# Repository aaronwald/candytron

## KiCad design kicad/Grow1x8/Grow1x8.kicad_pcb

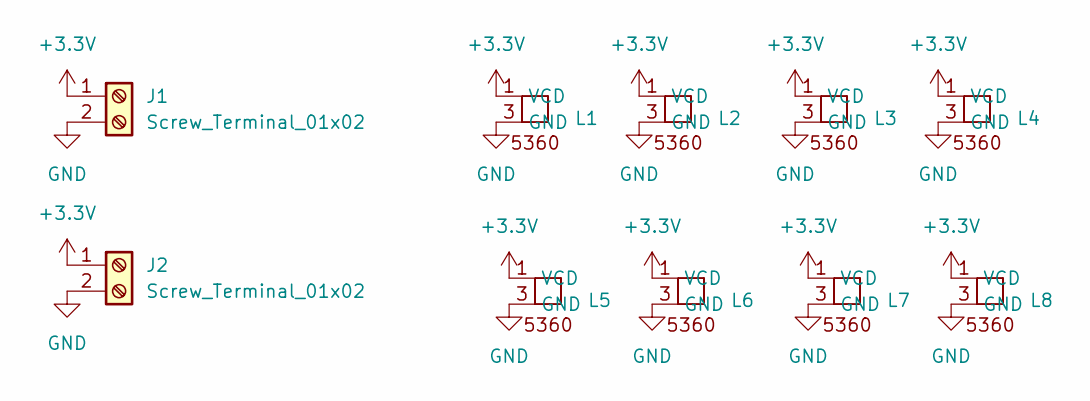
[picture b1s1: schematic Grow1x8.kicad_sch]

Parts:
J1, J2: Screw_Terminal_01x02; TerminalBlock_MetzConnect_Type011_RT05502HBWC_1x02_P5.00mm_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
L1, L2, L3, L4, L5, L6, L7, L8: LED 5630

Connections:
+3.3V: J1.1, J2.1, L1.1 (VCD), L2.1 (VCD), L3.1 (VCD), L4.1 (VCD), L5.1 (VCD), L6.1 (VCD), L7.1 (VCD), L8.1 (VCD)
GND: J1.2, J2.2, L1.3 (GND), L2.3 (GND), L3.3 (GND), L4.3 (GND), L5.3 (GND), L6.3 (GND), L7.3 (GND), L8.3 (GND)

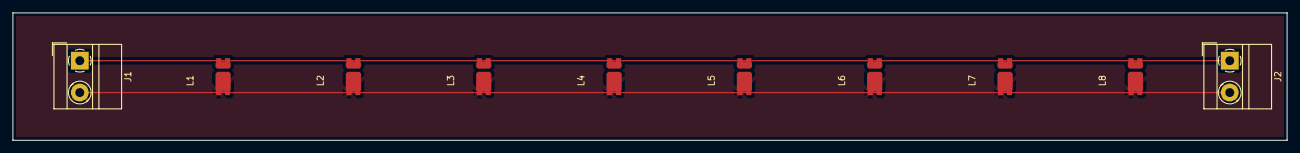
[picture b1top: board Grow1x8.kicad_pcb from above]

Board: 2 copper layers, 200.0 x 20.0 mm, 10 parts (0 on the bottom side), 2 nets.

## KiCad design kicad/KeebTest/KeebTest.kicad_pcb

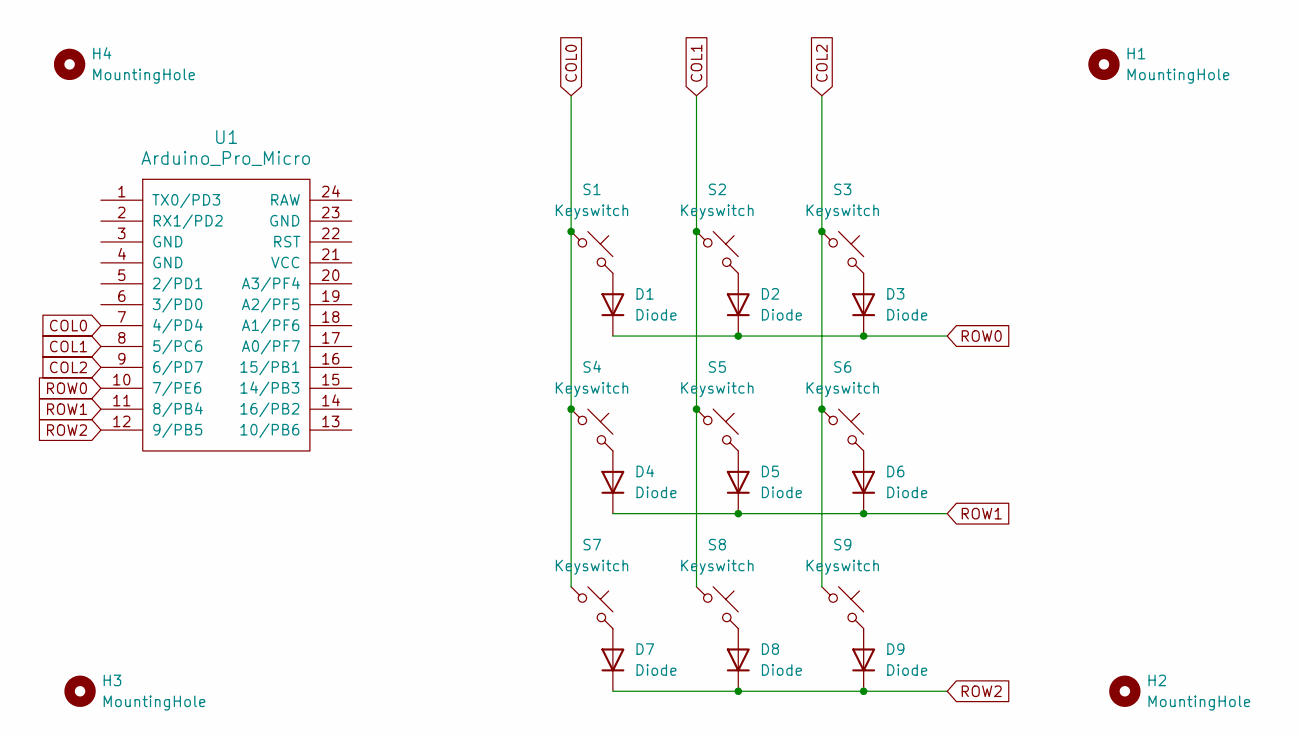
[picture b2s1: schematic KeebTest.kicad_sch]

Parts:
D1, D2, D3, D4, D5, D6, D7, D8, D9: Diode; Diode_DO-35
H1, H2, H3, H4: MountingHole; MountingHole_2.1mm
S1, S2, S3, S4, S5, S6, S7, S8, S9: Keyswitch; MX_PCB_1.00u
U1: Arduino_Pro_Micro

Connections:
COL0: S1.1, S4.1, S7.1, U1.7 (4/PD4)
COL1: S2.1, S5.1, S8.1, U1.8 (5/PC6)
COL2: S3.1, S6.1, S9.1, U1.9 (6/PD7)
unnamed: D1.2 (A), S1.2
unnamed: D2.2 (A), S2.2
unnamed: D3.2 (A), S3.2
unnamed: D4.2 (A), S4.2
unnamed: D5.2 (A), S5.2
unnamed: D6.2 (A), S6.2
unnamed: D7.2 (A), S7.2
unnamed: D8.2 (A), S8.2
unnamed: D9.2 (A), S9.2
ROW0: D1.1 (K), D2.1 (K), D3.1 (K), U1.10 (7/PE6)
ROW1: D4.1 (K), D5.1 (K), D6.1 (K), U1.11 (8/PB4)
ROW2: D7.1 (K), D8.1 (K), D9.1 (K), U1.12 (9/PB5)

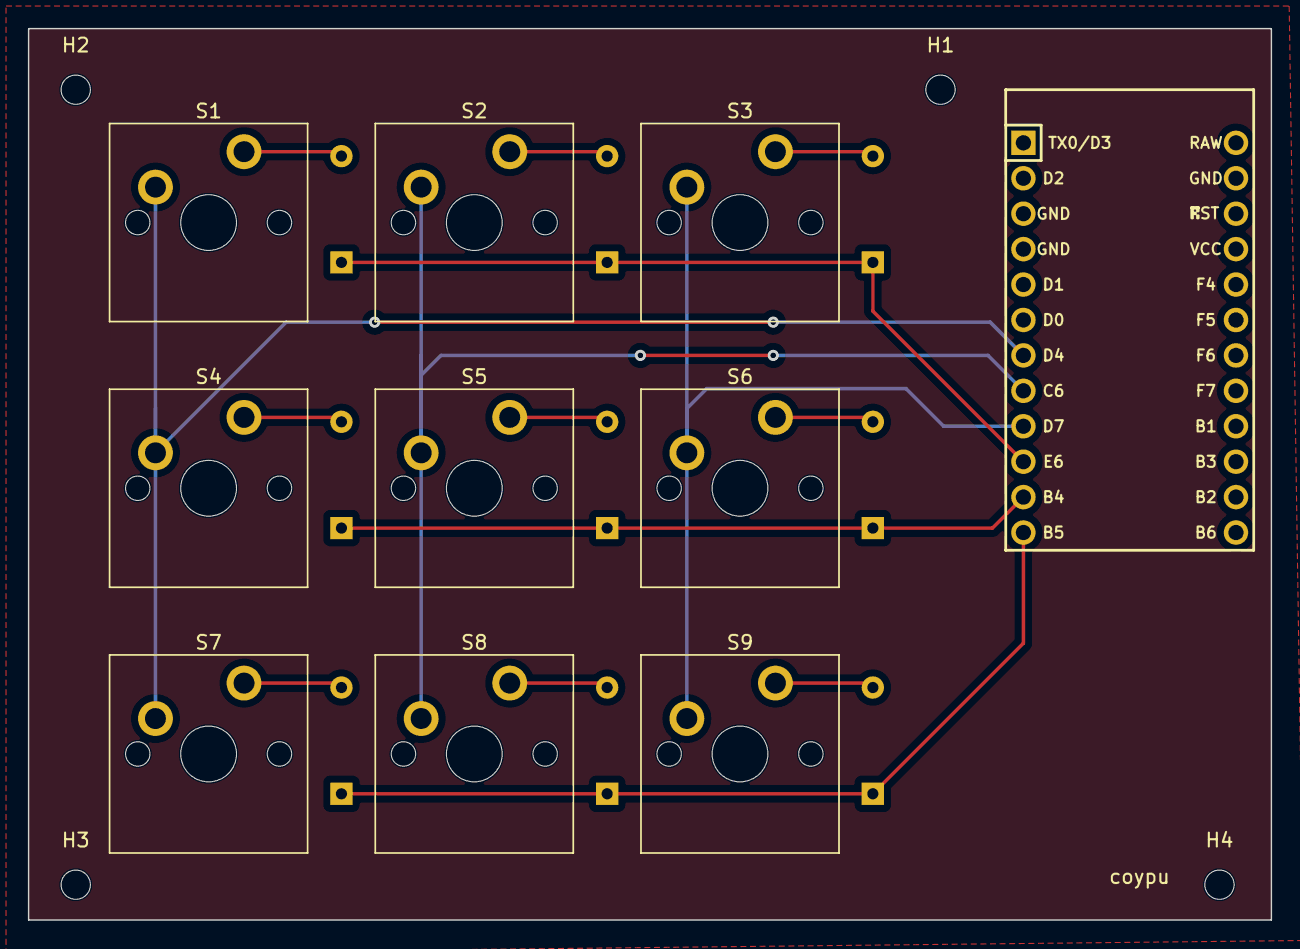
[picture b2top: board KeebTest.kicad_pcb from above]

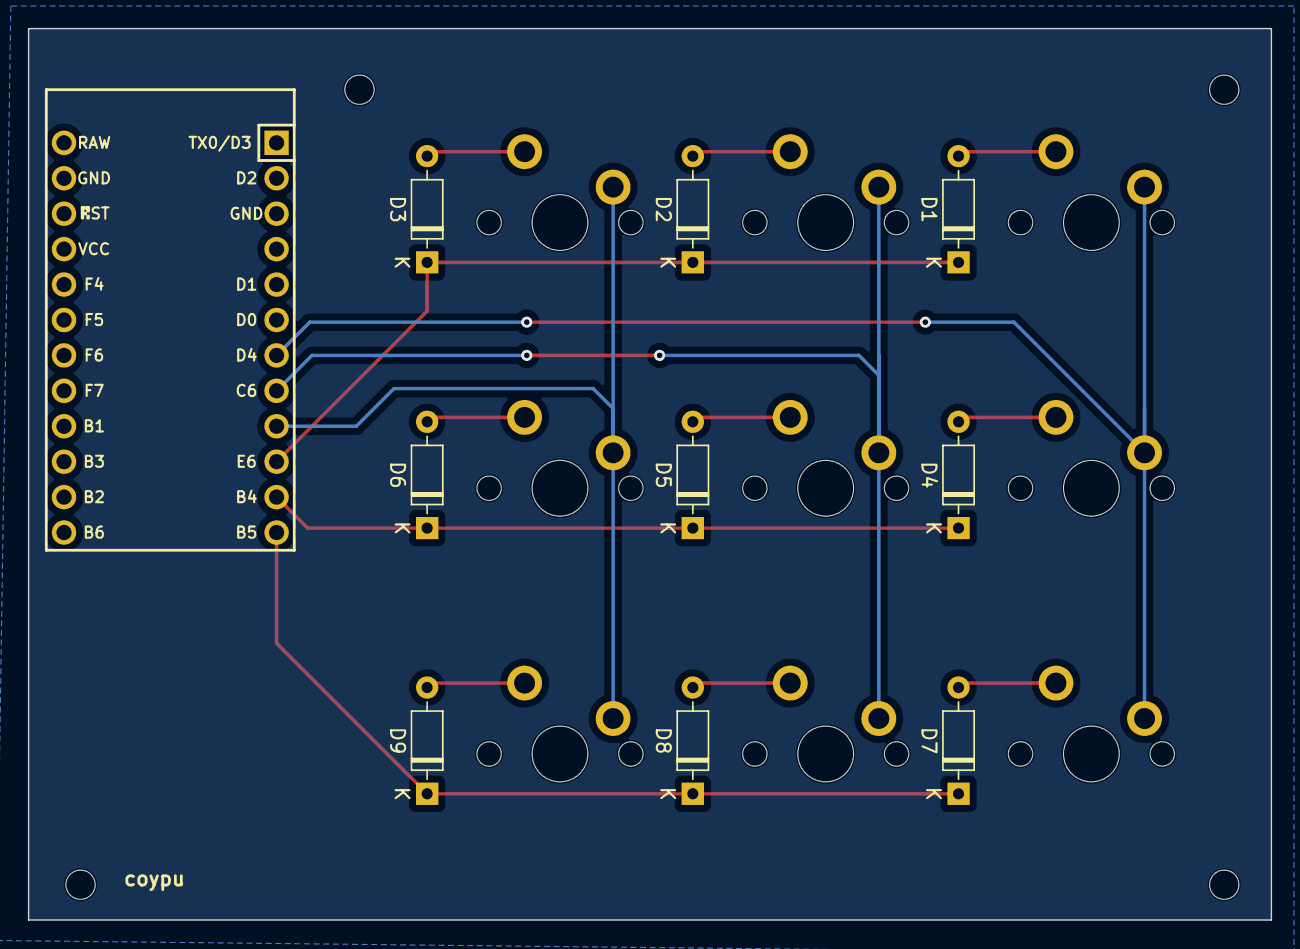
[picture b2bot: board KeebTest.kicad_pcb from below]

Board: 2 copper layers, 89.1 x 63.9 mm, 23 parts (9 on the bottom side), 15 nets.

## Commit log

2019-09-02 simple blink
2019-09-02 read single char from button
2019-09-02 read char
2019-09-07 test cube
2019-09-21 print gear
2019-09-22 latesT
2019-09-22 add readme
2019-09-28 dowel gears
2019-09-28 add license for gears
2019-09-28 add init code
2019-09-29 add paddle
2019-09-29 6 fin paddle
2019-10-20 paddel4
2019-10-20 cand
2019-10-23 tread dowel gear
2019-10-27 startup logic
2019-11-28 icestick revival
2019-12-16 shift test
2022-07-23 first good
2022-07-24 letters
2022-09-10 change to loop
2022-09-10 set output dir
2022-09-10 fix depth
2022-09-25 latest arduino
2023-04-09 lab3
2023-04-09 hello world - vid4
2023-11-25 add test
2023-11-25 basic ticker
2023-11-26 add queue and conflation
2023-11-26 add pairs
2023-11-26 refactor and set hostname
2023-11-26 add up/down arrows
2023-12-23 scotto test
2023-12-23 update size
2024-01-16 5/8" mitre bar
2024-03-23 samsung 5630 footprint mark I
2024-03-23 Combine pads into one
2024-03-23 kicad
2024-03-24 update gitignore
2024-03-24 add symbol
2024-08-24 add grow1
2024-08-24 update comments
